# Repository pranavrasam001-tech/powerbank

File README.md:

# Mini Power Bank PCB Design

## About the Project

I designed this Mini Power Bank PCB using KiCad to understand how a lithium-ion battery charging and power management circuit is designed from scratch. The board combines a TP4056 charging circuit, a DW01A battery protection circuit, and a MIC2290 boost converter to provide a nominal 5V output.

The design focuses on battery charging, protection, and voltage conversion without using a microcontroller. I worked on the schematic, component footprint assignment, PCB placement, routing, and preparation of manufacturing files.

## Features

* USB Type-C charging input
* Single-cell lithium-ion battery charging
* Battery overcharge and over-discharge protection
* Overcurrent protection through the battery protection circuit
* 5V output using a DC-DC boost converter
* Dedicated battery charging and protection ICs
* Compact PCB layout
* No microcontroller or firmware required for basic operation
* Designed using KiCad

## Tools and Components Used

**Software:**

* KiCad
* PCB fabrication tools for generating Gerber and drill files

**Components:**

* TP4056 lithium-ion battery charger
* DW01A battery protection IC
* MIC2290 boost converter
* MOSFETs for battery protection
* USB Type-C connector
* Inductor
* Resistors
* Capacitors
* LED
* Battery connector

## What I Did

* Researched the components required for a basic power bank circuit.
* Studied the functions of the battery charging, protection, and boost converter sections.
* Created the circuit schematic in KiCad.
* Connected the TP4056 charging circuit to the battery interface.
* Designed the DW01A battery protection section with external MOSFETs.
* Added the MIC2290 boost converter and its associated components.
* Assigned footprints to the schematic components.
* Transferred the components into PCB Editor.
* Arranged the components within the board outline.
* Started routing the PCB connections.
* Reviewed component placement, spacing, and orientation.
* Generated Gerber, drill, and component placement files for manufacturing.

## PCB Design Preview

### 1. Circuit Schematic

The schematic illustrates the battery charging circuit, protection network, and boost converter, along with their associated components and connections.

### 2. PCB Layout

The PCB layout shows the component placement, copper tracks, and board arrangement.

### 3. 3D PCB View

The 3D view provides a visual representation of the board and helps review component orientation, spacing, connector placement, and mechanical arrangement.

## Applications

This design can serve as a starting point for learning and experimenting with:

* Portable power supply circuits
* Lithium-ion battery charging
* Battery protection systems
* DC-DC boost converters
* USB-powered electronic devices
* Power management circuit design
* PCB design and electronics prototyping

**Note:** The design must be electrically verified and the assembled board tested before it can be considered a working power bank. Actual output current and performance depend on the selected components, battery, thermal conditions, and PCB layout.

## What I Learned

Working on this project helped me understand how different power management circuits operate together.

I learned how to:

* Design a battery charging schematic.
* Understand lithium-ion battery protection using a dedicated protection IC and MOSFETs.
* Work with a DC-DC boost converter.
* Verify MOSFET gate, source, and drain connections.
* Check component pinouts and footprints against datasheets.
* Assign footprints and arrange components in KiCad.
* Route PCB tracks and review board connectivity.
* Use ERC and DRC to identify design issues.
* Generate manufacturing files for PCB fabrication.

## Bill of Materials (BOM)

| Designator | Value | Footprint | LCSC Part # | Type | Manufacturer | MPN | Order Qty (5 pcs) | Price (USD) | X (mm) | Y (mm) | Rot |
|---|---|---|---|---|---|---|---|---|---|---|---|
| BT1 | Battery_Cell | BatteryHolder_Keystone_3000_1x12mm | C238097 | Extended | Keystone | 3000 | 5 | 1.709 | 152.2 | -102.8 | 0.0 |
| C3 | 100nF | C_0603_1608Metric | C14663 | Basic | YAGEO | CC0603KRX7R9BB104 | 5 | 0.042 | 147.9375 | -118.8 | 90.0 |
| D1 | LED | LED_0603_1608Metric | C99290 | Extended | Lite-On | LTST-C191TBKT | 20 | 0.426 | 126.275 | -121.0025 | 90.0 |
| J1 | USB_C_Receptacle_PowerOnly_6P | USB_C_Receptacle_HRO_TYPE-C-31-M-12 | C165948 | Extended | Korean Hroparts Elec | TYPE-C-31-M-12 | 5 | 0.934 | 134.11 | -97.2 | 180.0 |
| L1 | 10µH | L_Bourns_SRR1260 | C3221699 | Extended | BOURNS | SRR1260-100M | 5 | 4.6695 | 137.2 | -133.8 | 0.0 |
| Q1 | Q_NMOS_GSD | SOT-23-6 | C908265 | Extended | FUXINSEMI | FS8205A | 14 | 1.0038 | 157.6625 | -126.4 | 0.0 |
| Q2 | Q_NMOS_GSD | SOT-23-6 | C908265 | Extended | FUXINSEMI | FS8205A |  |  | 150.4625 | -126.4 | 0.0 |
| R1 | 5.1k | R_0603_1608Metric | C23186 | Basic | UNI-ROYAL(Uniroyal Elec) | 0603WAF5101T5E | 10 | 0.015 | 131.9 | -120.59 | 0.0 |
| R2 | 5.1k | R_0603_1608Metric | C23186 | Basic | UNI-ROYAL(Uniroyal Elec) | 0603WAF5101T5E |  |  | 131.6 | -105.4 | 0.0 |
| R3 | 2.2k | R_0603_1608Metric | C4190 | Basic | UNI-ROYAL(Uniroyal Elec) | 0603WAF2201T5E | 5 | 0.009 | 126.075 | -115.19 | 90.0 |
| R4 | 1.2kΩ | R_0603_1608Metric | C22765 | Basic | UNI-ROYAL(Uniroyal Elec) | 0603WAF1201T5E | 5 | 0.017 | 141.875 | -113.565 | 90.0 |
| R5 | 15k | R_0603_1608Metric | C22809 | Basic | UNI-ROYAL(Uniroyal Elec) | 0603WAF1502T5E | 5 | 0.0145 | 148.3 | -139.075 | 90.0 |
| R6 | 4.99k | R_0603_1608Metric | C23046 | Basic | UNI-ROYAL(Uniroyal Elec) | 0603WAF4991T5E | 5 | 0.0105 | 155.5 | -139.825 | 90.0 |
| R7 | 100Ω | R_0603_1608Metric | C22775 | Basic | UNI-ROYAL(Uniroyal Elec) | 0603WAF1000T5E | 5 | 0.0115 | 126.75 | -134.225 | 90.0 |
| U1 | TP4056-42-ESOP8 | SOIC-8-1EP_3.9x4.9mm_P1.27mm_EP2.41x3.3mm_ThermalVias | C16581 | Extended | TOPPOWER(Nanjing Extension Microelectronics) | TP4056-42-ESOP8 | 5 | 0.9265 | 134.475 | -114.765 | 0.0 |
| U2 | DW01A | SOT-23-6 | C351410 | Extended | PUOLOP | DW01A | 9 | 0.4788 | 154.5375 | -118.6 | 0.0 |
| U3 | MIC2290 | Micrel_MLF-8-1EP_2x2mm_P0.5mm_EP0.8x1.3mm_ThermalVias | C144214 | Extended | Microchip Tech | MIC2290YML-TR | 5 | 8.455 | 152.3 | -135.65 | 0.0 |
| C1 | 2.2µF | C_0603_1608Metric | C9900011780 | Extended | JLCPCB Assembly | cap,2.2uF,+/-10%,25V,X5R,C0603 | 20 | 0.014 | 128.475 | -112.215 | 90.0 |
| C2 | 22µF | C_0805_2012Metric | C9900276340 | Extended | JLCPCB Assembly | 22uF 10V C-0805 | 9 | 0.3582 | 157.0 | -134.8 | 90.0 |
| **Parts total - JLCPCB BOM match (5 boards)** | | | | | | | | **19.0943** | | | |
| **PCB (5 pcs, 2 layers, 1.6mm, HASL with lead, green)** | | | | | | | | **4.00** | | | |
| **PCBA setup fee** | | | | | | | | **8.24** | | | |
| **PCBA stencil** | | | | | | | | **1.55** | | | |
| **PCBA components (11 items)** | | | | | | | | **10.41** | | | |
| **PCBA extended components fee** | | | | | | | | **9.27** | | | |
| **PCBA SMT assembly** | | | | | | | | **0.45** | | | |
| **PCBA nitrogen reflow soldering** | | | | | | | | **0.91** | | | |
| **PCBA subtotal (economic, top side)** | | | | | | | | **30.83** | | | |
| **Merchandise total (PCB + PCBA)** | | | | | | | | **34.83** | | | |
| **Shipping** | | | | | | | | **9.83** | | | |
| **Coupon** | | | | | | | | **-10.00** | | | |
| **Order subtotal** | | | | | | | | **34.66** | | | |

## Firmware Requirements

This design does not require firmware because the TP4056, DW01A, and MIC2290 perform their functions through dedicated hardware circuitry.

A microcontroller would only be required if additional programmable features were introduced, such as a digital battery percentage display, software-based monitoring, or programmable power management.

## Project Status

The schematic and PCB design have been developed in KiCad, and manufacturing files have been generated.

Further verification is required to confirm all component connections, footprints, battery protection functions, boost converter operation, and PCB design rules before fabrication and testing.

## Safety Considerations

Lithium-ion batteries require correct charging limits, suitable protection circuitry, and proper electrical connections.

Before powering the circuit:

* Verify the battery polarity and voltage ratings.
* Check the TP4056 charging configuration.
* Verify the DW01A sensing network and MOSFET connections.
* Confirm that battery negative and protected output negative follow the intended protection topology.
* Check the MIC2290 component values and layout recommendations.
* Inspect the PCB for shorts and incorrect connections.
* Test the charging and output stages under controlled conditions.

Do not connect a battery or valuable electronic device until the circuit has been reviewed and checked for faults.

```

The folder structure is a suggested organization for the project repository. Update the filenames and folders to match the files actually included in the repository.

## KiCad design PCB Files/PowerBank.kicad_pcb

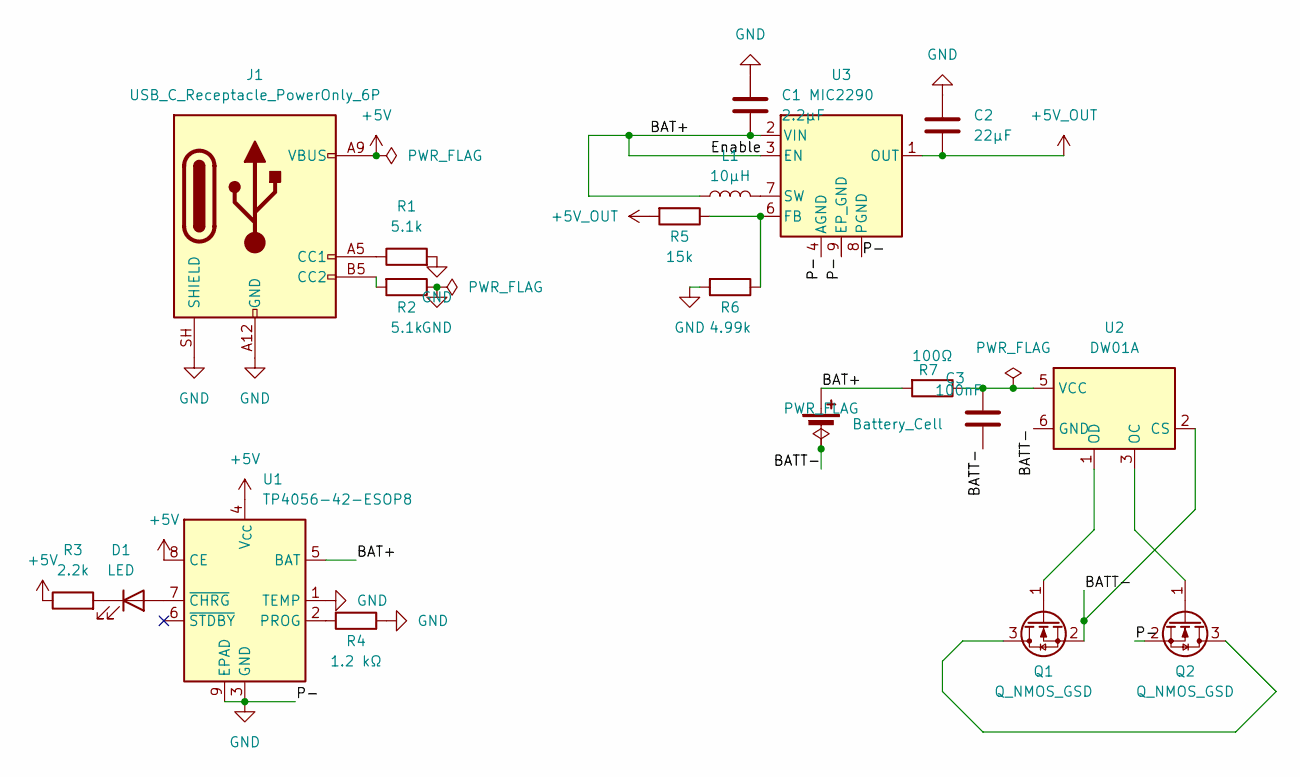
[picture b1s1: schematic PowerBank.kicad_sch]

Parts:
BT1: Battery_Cell; BatteryHolder_Keystone_3000_1x12mm
C1: 2.2µF; C_0603_1608Metric
C2: 22µF; C_0805_2012Metric
C3: 100nF; C_0603_1608Metric
D1: LED; LED_0603_1608Metric
J1: USB_C_Receptacle_PowerOnly_6P; USB_C_Receptacle_HRO_TYPE-C-31-M-12
L1: 10µH; L_Bourns_SRR1260
Q1, Q2: Q_NMOS_GSD; SOT-23-6
R1, R2: 5.1k; R_0603_1608Metric
R3: 2.2k; R_0603_1608Metric
R4: 1.2 kΩ; R_0603_1608Metric
R5: 15k; R_0603_1608Metric
R6: 4.99k; R_0603_1608Metric
R7: 100Ω; R_0603_1608Metric
U1: TP4056-42-ESOP8; SOIC-8-1EP_3.9x4.9mm_P1.27mm_EP2.41x3.3mm_ThermalVias
U2: DW01A; SOT-23-6
U3: MIC2290; Micrel_MLF-8-1EP_2x2mm_P0.5mm_EP0.8x1.3mm_ThermalVias

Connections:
+5V: J1.A9 (VBUS), J1.B9 (VBUS), R3.1, U1.4 (V_{CC}), U1.8 (CE)
+5V_OUT: C2.2, R5.2, U3.1 (OUT)
/BAT+: BT1.1 (+), C1.2, L1.1, R7.2, U1.5 (BAT), U3.2 (VIN), U3.3 (EN)
/BATT-: BT1.2 (-), C3.2, Q1.2 (S), U2.2 (CS), U2.6 (GND)
GND: C1.1, C2.1, J1.A12 (GND), J1.B12 (GND), J1.SH (SHIELD), Q2.2 (S), R1.2, R2.1, R4.1, R6.2, U1.1 (TEMP), U1.3 (GND), U1.9 (EPAD), U3.4 (AGND), U3.8 (PGND), U3.9 (EP_GND)
unnamed: D1.2 (A), U1.7 (~CHRG)
unnamed: D1.1 (K), R3.2
unnamed: J1.A5 (CC1), R1.1
unnamed: J1.B5 (CC2), R2.2
unnamed: Q1.3 (D), Q2.3 (D)
unnamed: Q1.1 (G), U2.1 (OD)
unnamed: Q2.1 (G), U2.3 (OC)
unnamed: R4.2, U1.2 (PROG)
unnamed: C3.1, R7.1, U2.5 (VCC)
unnamed: R5.1, R6.1, U3.6 (FB)
unnamed: L1.2, U3.7 (SW)

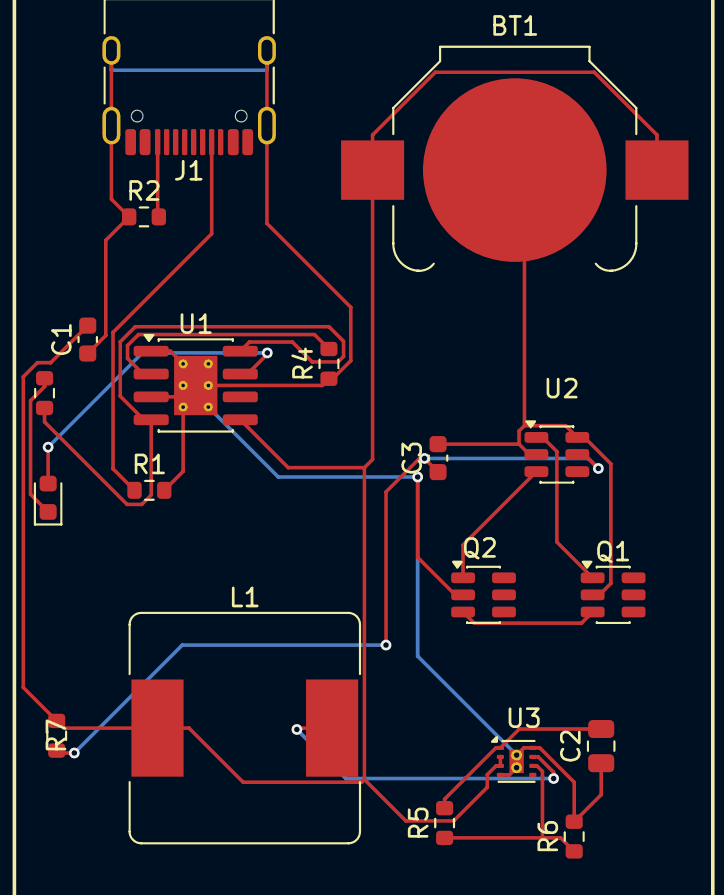
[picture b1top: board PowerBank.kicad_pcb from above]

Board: 2 copper layers, 19 parts (0 on the bottom side), 16 nets.
